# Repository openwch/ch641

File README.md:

# PD Wireless Charging Specialized Microcontroller CH641
EN | [中文](README_zh.md)

### Overview
CH641 series is a dedicated microcontroller for PD wireless charging designed based on barley RISC-V2A core. This series has the characteristics of wide voltage, single line debugging, low power consumption and compact peripheral.
CH641 built-in PD PHY, BC interface, differential input current sampling and AC small signal amplification decoder.
The CH641 has built-in PD PHY, BC interface, differential input current sampling and AC small signal amplifier/decoder, supports USB PD and Type C fast charging, BC1.2 and DCP and other HV charging protocols, and provides DMA controller, 10-bit ADC, multi-group timer and DMA controller.
DMA controller, 10-bit analog-to-digital converter ADC, multi-group timer, USART serial port, I2C and other rich peripheral resources, over-voltage protection and over-temperature protection.

### Features
- Qingke 32-bit RISC-V2A Core
- Fast Programmable Interrupt Controller + Hardware Interrupt Stacks
- Supports 2 levels of interrupt nesting
- Support system main frequency 48MHz
- 2KB SRAM，16KB CodeFlash，1920B BootLoader
- 64B System Non-Volatile Configuration Information Storage Area
- 64B User-defined information storage area
- System power supply VHV rated voltage: 5V ~ 12V
- Low power consumption modes: sleep, standby
- Built-in factory-tuned 24MHz RC oscillator
- Built-in low frequency RC oscillator
- Power-on reset, programmable voltage monitor
- 7 DMA channels with ring buffer management support
- Support TIM1/ADC/USART/I2C
- Analog input range: GND to 3.3V
- 15 external signal signals + 1 internal signal channel
- Supports external delayed triggering
- 1 x 16-bit advanced timer providing deadband control and emergency
- 1 x 16-bit streamlined general purpose timer
- 1 watchdog timer (window type)
- System time base timer: 32-bit counter
- A set of multi-pin mapped USART serial ports
- 1 I2C slave interface
- Support for DRP, Sink and Source applications
- 3 CC pins, some CC pins have built-in Rd
- Supports BC1.2 and multiple HV DCP charging protocols
- Built-in 6-bit DAC, supports multiple voltage outputs and pull-downs
- Differential input current sampling ISP/ISN
- AC Small Signal Amplifier Decoder QII
- 2 sets of GPIO ports, 25 I/O ports
- external interrupt
- 4 high voltage drive pins, 5 low voltage strong drive pins
- OVP over-voltage protection and OTP over-temperature protection
- Security features: 64-bit chip unique ID
- Debugging mode: serial single-wire debugging interface
- Package: QFN, QSOP

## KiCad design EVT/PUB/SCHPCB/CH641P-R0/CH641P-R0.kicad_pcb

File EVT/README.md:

# EVT

### -- download URL
*  CH641EVT.ZIP-https://www.wch.cn/downloads/CH641EVT_ZIP.html

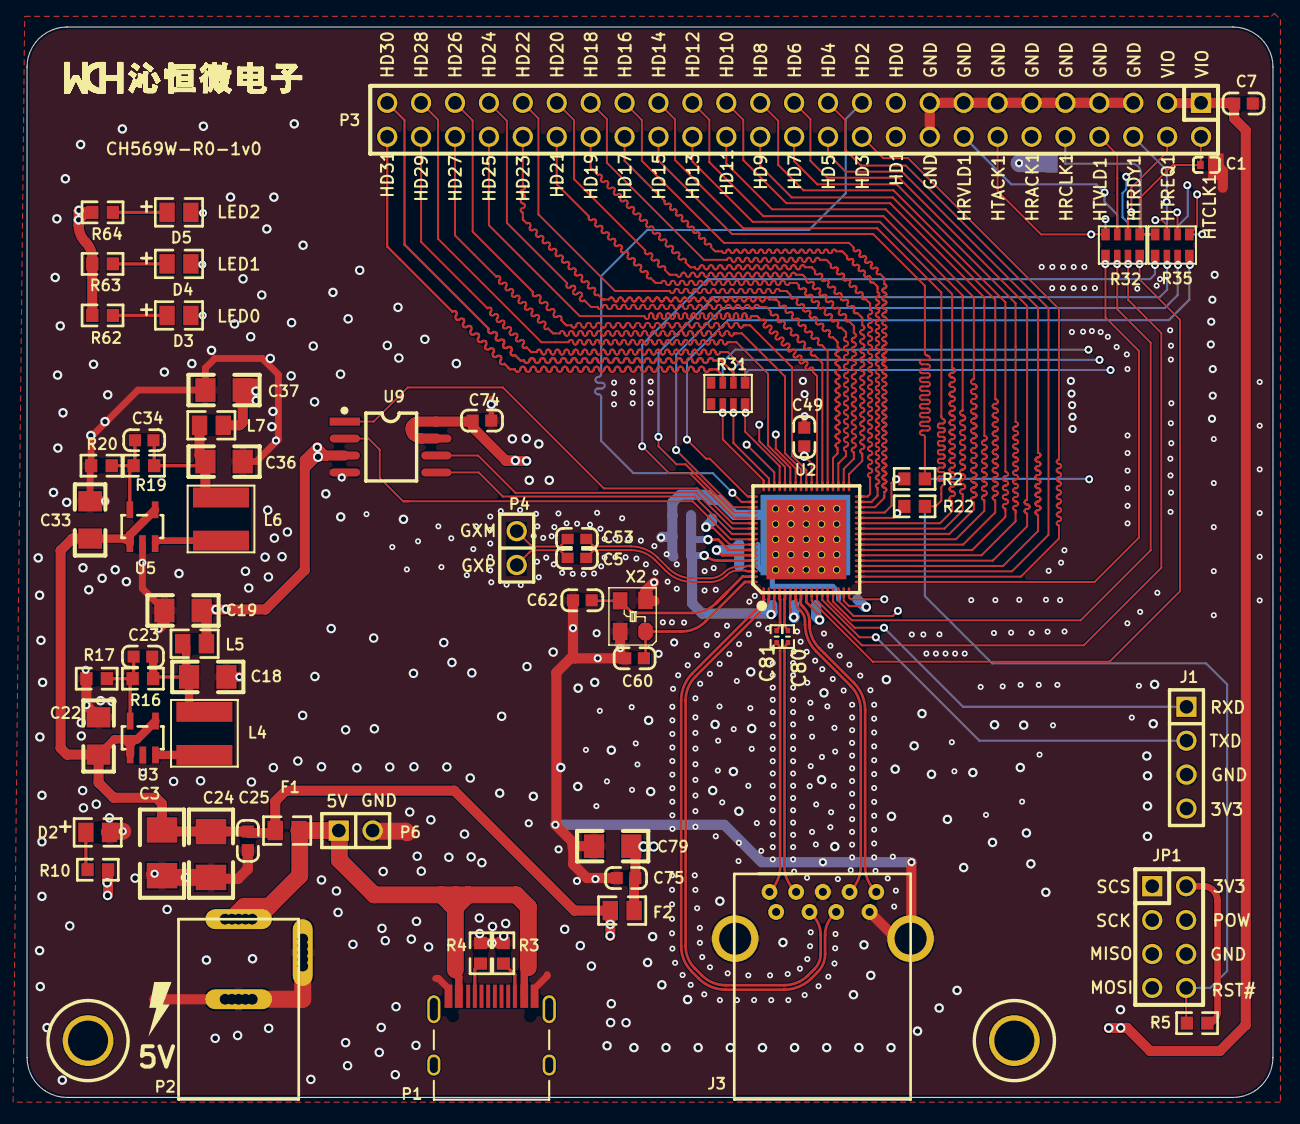
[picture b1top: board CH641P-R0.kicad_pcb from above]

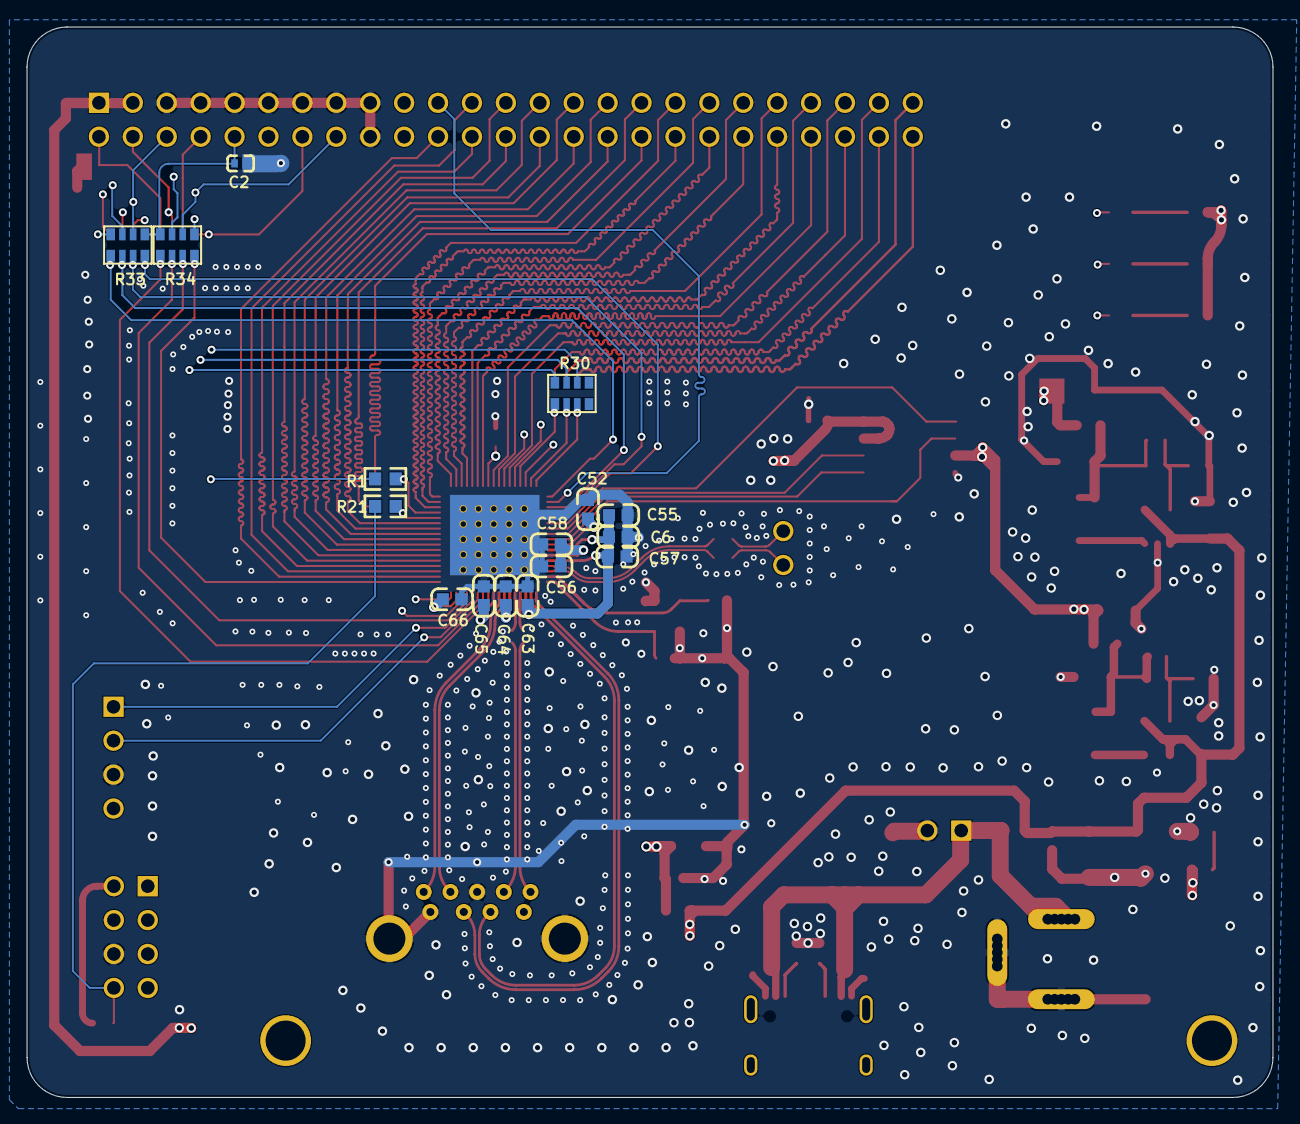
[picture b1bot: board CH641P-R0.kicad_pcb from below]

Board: 4 copper layers, 93.3 x 80.2 mm, 78 parts (16 on the bottom side), 99 nets.

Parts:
C1, C2: 20pF/NC; 0402C
C3, C24: 33uF; 3528
C5, C53: 104; 0603C
C6, C7, C25, C49, C52, C56, C57, C63, C64, C65, C66, C75: 100nF; 0603C
C18, C19, C22, C33, C36, C37, C79: 10uF; 3216
C23, C34, C60, C62: 20pF; 0603C
C55, C58: 3.3uF; 0603C
C74: 0.1uF; 0603C
C80, C81: 100nF; C 0402_L
D2: LED1; 0805+
D3: 翠绿; 0805+
D4: 蓝灯; 0805+
D5: 黄灯; 0805+
F1, F2: 1A; 0805
J1: CON4; SIP4-2.54mm
J3: USB-AF3.0; USB3.0-Receptacle
JP1: HEADER 4X2; IDC8-2.54mm
L4, L6: 3.3uH; SMD_5x5mm
L5, L7: 0Ω; 0805
P1: TYPE-C-Receptacle-2.0
P2: POWER_JACK; DC-005
P3: LEFT_P; IDC50-2.54mm
P4: HEADER 2; SIP2-2.54mm
P6: Header 2; SIP2-2.54mm
R1, R2, R21, R22: 0R; 0603
R3, R4: 5.1K/NC; 0603
R5, R16, R19, R20: 10K; 0603
R10, R62, R63, R64: 1K; 0603
R17: 2.2K; 0603
R30, R31, R32, R33, R34, R35: 0R; RCA-8P4R-0603
U2: CH569W; QFN68_8X8
U3, U5: 8502AM; SOT753
U9: W25Q32JV; SOIC-8_208mil
X2: 30MHz; 3225

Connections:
1V2: C37.2, C56.2, C58.2, C64.2, C65.2, L7.2, U2.6, U2.9, U2.63
3V3: C6.1, C19.2, C49.1, C52.2, C55.2, C57.2, C63.2, C66.2, C74.2, J1.4, JP1.2, L5.2, R5.2, R10.2, R62.2, R63.2, R64.2, U2.3, U2.16, U2.42, U2.61, U2.62, U2.64, U9.3, U9.7, U9.8
3X1-IN: C60.2, U2.68, X2.1
3X1-OUT: C62.1, U2.67, X2.3
GND: C1.1, C2.1, C3.1, C6.2, C7.2, C18.1, C19.1, C22.1, C24.2, C25.1, C33.1, C36.1, C37.1, C49.2, C52.1, C55.1, C56.1, C57.1, C58.1, C60.1, C62.2, C63.1, C64.1, C65.1, C66.1, C74.1, C75.2, C79.2, D2.2, J1.3, J3.0, J3.4, J3.7, JP1.6, P1.A1, P1.B1, P2.2, P2.3, P3.5, P3.7, P3.9, P3.11, P3.13, P3.15, P3.17, P3.18, P6.2, R3.2, R4.2, R17.1, R20.1, U2.0, U3.2, U5.2, U9.4, X2.2, X2.4
GXM: C53.1, U2.65
GXP: C5.1, U2.66
HD0: P3.19, U2.15
HD1: P3.20, U2.17
HD2: P3.21, U2.53
HD3: P3.22, U2.19
HD4: P3.23, U2.20
HD5: P3.24, U2.21
HD6: P3.25, U2.22
HD7: P3.26, U2.23
HD8: P3.27, U2.24
HD9: P3.28, U2.25
HD10: P3.29, U2.26
HD11: P3.30, U2.27
HD12: P3.31, U2.28
HD13: P3.32, U2.29
HD14: P3.33, R22.2
HD15: P3.34, R2.2
HD16: P3.35, U2.32
HD17: P3.36, U2.33
HD18: P3.37, U2.34
HD19: P3.38, U2.35
HD20: P3.39, U2.36
HD21: P3.40, U2.37
HD22: P3.41, U2.38
HD23: P3.42, U2.39
HD24: P3.43, U2.40
HD25: P3.44, U2.41
HD26: P3.45, U2.43
HD27: P3.46, U2.44
HD28: P3.47, U2.46
HD29: P3.48, R31.1
HD30: P3.49, R31.2
HD31: P3.50, R31.3
HRACK: R32.7, R34.2, U2.11
HRACK1: P3.12, R33.3, R34.7
HRCLK: R32.8, R34.1, U2.10
HRCLK1: C2.2, P3.10, R33.1, R34.8
HRVLD: R32.6, R34.3, U2.14
HRVLD1: P3.16, R33.4, R34.6
HTACK: R33.7, R35.2, U2.55
HTACK1: P3.14, R32.4, R35.7
HTCLK: R33.8, R35.1, U2.56
HTCLK1: C1.2, P3.2, R32.1, R35.8
HTRDY: R32.5, R34.4, U2.18
HTRDY1: P3.6, R33.2, R34.5
HTREQ: R33.6, R35.3, U2.54
HTREQ1: P3.4, R32.2, R35.6
HTVLD: R33.5, R35.4, U2.52
HTVLD1: P3.8, R32.3, R35.5
LED0: D3.2, U2.49
LED1: D4.2, U2.45
LED2: D5.2, U2.47
MISO: JP1.5, R1.2
MISO1: U2.60, U9.2
MOSI: JP1.7, R30.6
MOSI1: U2.59, U9.5
NetC5_2: C5.2, P4.2
NetC18_2: C18.2, C23.2, L4.2, L5.1, R16.1
NetC23_1: C23.1, R16.2, R17.2, U3.5
NetC34_1: C34.1, R19.2, R20.2, U5.5
NetC34_2: C34.2, C36.2, L6.2, L7.1, R19.1
NetC53_2: C53.2, P4.1
NetC75_1: C75.1, C79.1, F2.1, J3.1
NetC80_2: C80.2, J3.8
NetC81_2: C81.2, J3.9
NetD2_1: D2.1, R10.1
NetD3_1: D3.1, R62.1
NetD4_1: D4.1, R63.1
NetD5_1: D5.1, R64.1
NetF1_1: F1.1, P1.A4, P1.B4, P2.1, P6.1
NetL4_1: L4.1, U3.3
NetL6_1: L6.1, U5.3
NetP1_A5: P1.A5, R4.1
NetP1_B5: P1.B5, R3.1
PB11: R30.1, R31.8, U2.48
PB12: R30.2, R31.7, U2.50
PB13: R30.3, R31.6, U2.51
PB14: R1.1, R2.1, U2.31
PB15: R21.1, R22.1, U2.30
POW: C3.2, C7.1, C22.2, C24.1, C25.2, C33.2, F1.2, F2.2, JP1.4, P3.1, P3.3, U3.1, U3.4, U5.1, U5.4
RST#: JP1.8, R5.1, R21.2
RXD: J1.1, U2.13
SCK: JP1.3, R30.7
SCK1: U2.58, U9.6
SCS: JP1.1, R30.8
SCS1#: U2.57, U9.1
SSRX_N: J3.5, U2.8
SSRX_P: J3.6, U2.7
SSTX_N: C80.1, U2.5
SSTX_P: C81.1, U2.4
TXD: J1.2, U2.12
UD_N: J3.2, U2.2
UD_P: J3.3, U2.1

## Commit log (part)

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2023-10-30 ch641V1.0
2023-12-08 v1.0
2023-12-28 V1.1
2024-07-12 V1.2
2024-10-29 V1.3
2025-03-12 V1.4
